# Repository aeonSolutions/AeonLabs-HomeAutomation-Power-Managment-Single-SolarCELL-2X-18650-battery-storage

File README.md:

[PCB-Prototyping-Catalogue](https://github.com/aeonSolutions/PCB-Prototyping-Catalogue)  >>  [Home-Automation](https://github.com/aeonSolutions/PCB-Prototyping-Catalogue/tree/main/Home-Automation)  >>  [Smart Home Solar Power Management](https://github.com/aeonSolutions/PCB-Prototyping-Catalogue/tree/main/Home-Automation/Smart%20Home%20Solar%20Power%20Management)  >>   Single Solar Cell with two 18650 as Battery Storage

<br>

<p align="right">
 <a href="https://github-com.translate.goog/aeonSolutions/PCB-Prototyping-Catalogue/tree/main?_x_tr_sl=en&_x_tr_tl=pt&_x_tr_hl=en&_x_tr_pto=wapp">Change Language</a> <br>
Last update: 01-12-2023
</p>

# Single Solar Cell with two 18650 as Battery Storage
This is a simple PCB for a direct fit on commercially available 4V to 6V [black solar cell tiles](https://s.click.aliexpress.com/e/_DCSwB9L)  with dimensions up to 124mm wide. This PCB features two 18650 Battery management system intended for indoor usage. In particular to be installed on the top or downside of transparent glass windows at a home or office. This PCB, when assembled with a blue solar cell tile, can be used to power a low voltage 4.2V indoor illumination network using ultra-low power micro LED strips.  For instance [this one](https://s.click.aliexpress.com/e/_DCKg9xJ) sold on AliExpress.   

When connected in series and installed on several windows and networked, can power off the grid with a 4.2V LED illumination on all rooms and compartments at a home or office. During evenings and at night until bedtime. If one intends to use it to power indoors LED illumination during the day is required a High Capacity Power Bank connected to all first tiles of all the series. For instance this [power bank](https://s.click.aliexpress.com/e/_Ddl7nsh) here. 

One important takeway about this prototype project is the ability to be installed on any traditional apartment or home in a big city, requiring  124mm of window glass estate, at the top or at the bottom. And it can connect to existing home automation network or systems. If you prefer, can read this project on Autodesk's Instructables.com website [here](https://www.instructables.com/Single-Solar-Cell-With-Two-18650-As-Battery-Storag/).

<p align="center">

</p>

A brief view of specifications:

- 2x 18650 LiPo battery management system
- the PCB can be connected in series to form a length of solar cell tiles packed together (each with its own single BMS.
- Main ON/OFF switch.
- PCB assembly in series made with a 10-pin header/ socket. For "plug and play" type of installations
- Screw terminal to connect main low power 5V DC line at home/office.

<br>

**Status**

This PCB electronics is now fully tested and working when connected to a 5V solar tile and is able to charge a 4.2V LiPo battery. Mind you, this is the simplest electronics, with a restriction, one of being only useful for 24H energy storage (LiPo), meaning this electronics is only capable of managing the solar electricity collected during the day, to run during evenings and also at night until the battery is depleted. Therefore is suited for indoor LED illumination and even suited to power small smart electronics/devices. 

<br>

## PCB

<br>

## Compatibility

<p align="center">

</p>

<br>

## What one additionally needs
-  home tools
-  [transparent double sided tape](https://s.click.aliexpress.com/e/_DDJxMmD)
-  [blue solar cell tiles](https://s.click.aliexpress.com/e/_DCnJW0V)
-  [ultra-low power micro LED strips](https://s.click.aliexpress.com/e/_DCKg9xJ) 
-  [ultra-low power  LED Cob strips](https://s.click.aliexpress.com/e/_DnqkC4N)
-  [Nylon Guide for Electric Cable](https://s.click.aliexpress.com/e/_DBc1oVX)
-  [NCR18650B 3.7V 3400 mah 18650 Lithium](https://s.click.aliexpress.com/e/_DCh1sw1)
-  [Low power electrical wire](https://s.click.aliexpress.com/e/_DB1T3eN)
-  [16A Electrical Plug Wall Socket 110~250V Dual USB 2000mA Port](https://s.click.aliexpress.com/e/_DlVz3sh)
-  [Soldering iron](https://s.click.aliexpress.com/e/_DnDN8x3)
-  [Solder](https://s.click.aliexpress.com/e/_DlXtKMN)
- [power bank](https://s.click.aliexpress.com/e/_Ddl7nsh) 

<br />
<br />

## Author

You can get in touch with me on my LinkedIn Profile:

#### Miguel Tomas

You can also follow my GitHub Profile to stay updated about my latest projects: 

<br>

### Be supportive of my dedication and work towards technology education and buy me a cup of coffee
The PCB Desgin Files i provide here for anyone to use are free. If you like this Smart Device or use it, please consider buying me a cup of coffee, a slice of pizza or a book to help me study, eat and think new PCB design files.

<br />

### Make a donation on Paypal
Make a donation on paypal and get a TAX refund*.

<br>

### Support all these open hardware projects and become a patreon  
Liked any of my PCB KiCad Designs? Help and Support my open work to all by becomming a LDAD Patreon.
In return I will give a free PCB design in KiCad to all patreon supporters. To learn more go to patreon.com. Link below.

<br />
<br />

______________________________________________________________________________________________________________________________
### License
Before proceeding to download any of AeonLabs software solutions for open-source development and/or PCB hardware electronics development make sure you are choosing the right license for your project. See [AeonLabs Solutions for Open Hardware & Source Development](https://github.com/aeonSolutions/PCB-Prototyping-Catalogue/wiki/AeonLabs-Solutions-for-Open-Hardware-&-Source-Development) for more information.

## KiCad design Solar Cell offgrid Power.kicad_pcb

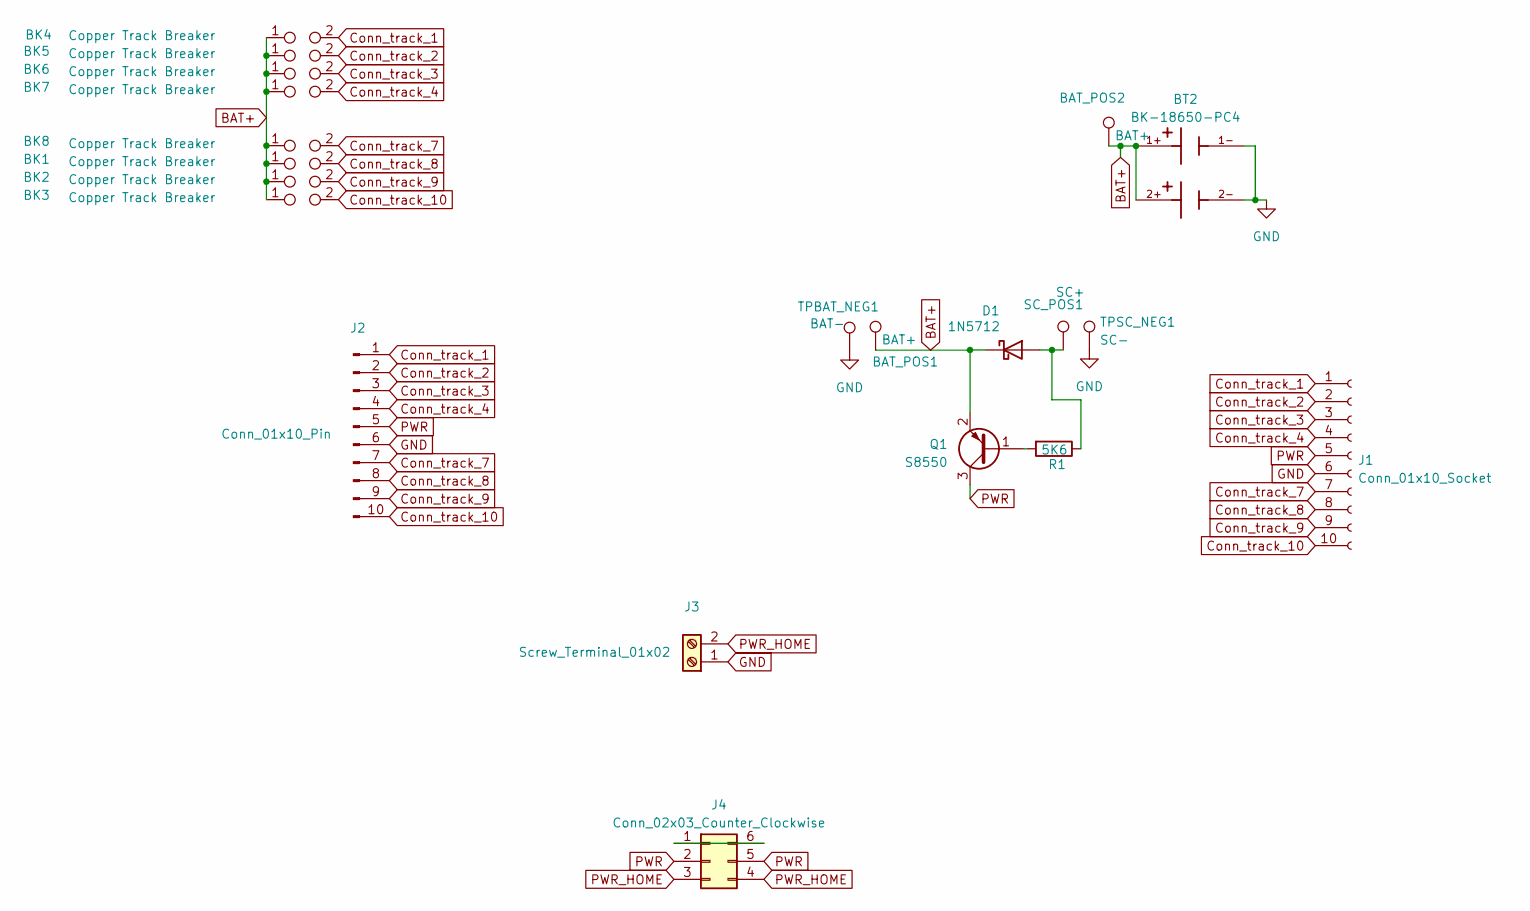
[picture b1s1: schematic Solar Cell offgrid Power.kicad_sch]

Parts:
BAT_POS1, BAT_POS2: BAT+; TestPoint_Pad_3.0x3.0mm
BK1, BK2, BK3, BK4, BK5, BK6, BK7, BK8: Copper Track Breaker; Copper Track Breaker 2 points
BT2: BK-18650-PC4; 2x 18650 Battery holder BAT_BK-18650-PC4; PARTREV K
D1: 1N5712; D_SOD-123
J1: Conn_01x10_Socket; PinSocket_1x10_P2.54mm_Horizontal
J2: Conn_01x10_Pin; PinHeader_1x10_P2.54mm_Horizontal
J3: Screw_Terminal_01x02; TerminalBlock_Phoenix_MPT-0,5-2-2.54_1x02_P2.54mm_Horizontal
J4: Conn_02x03_Counter_Clockwise; Toggle Switch 2 pos PCB MSS-22D18G2 2P2T
Q1: S8550; SOT-23-3
R1: 5K6; R_1210_3225Metric
SC_POS1: SC+; TestPoint_Pad_3.0x3.0mm
TPBAT_NEG1: BAT-; TestPoint_Pad_3.0x3.0mm
TPSC_NEG1: SC-; TestPoint_Pad_3.0x3.0mm

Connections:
BAT+: BAT_POS1.1, BAT_POS2.1, BK1.1, BK2.1, BK3.1, BK4.1, BK5.1, BK6.1, BK7.1, BK8.1, BT2.1+, BT2.2+, D1.1 (K), Q1.2 (E)
Conn_track_1: BK4.2, J1.1, J2.1
Conn_track_2: BK5.2, J1.2, J2.2
Conn_track_3: BK6.2, J1.3, J2.3
Conn_track_4: BK7.2, J1.4, J2.4
Conn_track_7: BK8.2, J1.7, J2.7
Conn_track_8: BK1.2, J1.8, J2.8
Conn_track_9: BK2.2, J1.9, J2.9
Conn_track_10: BK3.2, J1.10, J2.10
GND: BT2.1-, BT2.2-, J1.6, J2.6, J3.1, TPBAT_NEG1.1, TPSC_NEG1.1
unnamed: D1.2 (A), R1.1, SC_POS1.1
unnamed: J4.1, J4.6
unnamed: Q1.1 (B), R1.2
PWR: J1.5, J2.5, J4.2, J4.5, Q1.3 (C)
PWR_HOME: J3.2, J4.3, J4.4

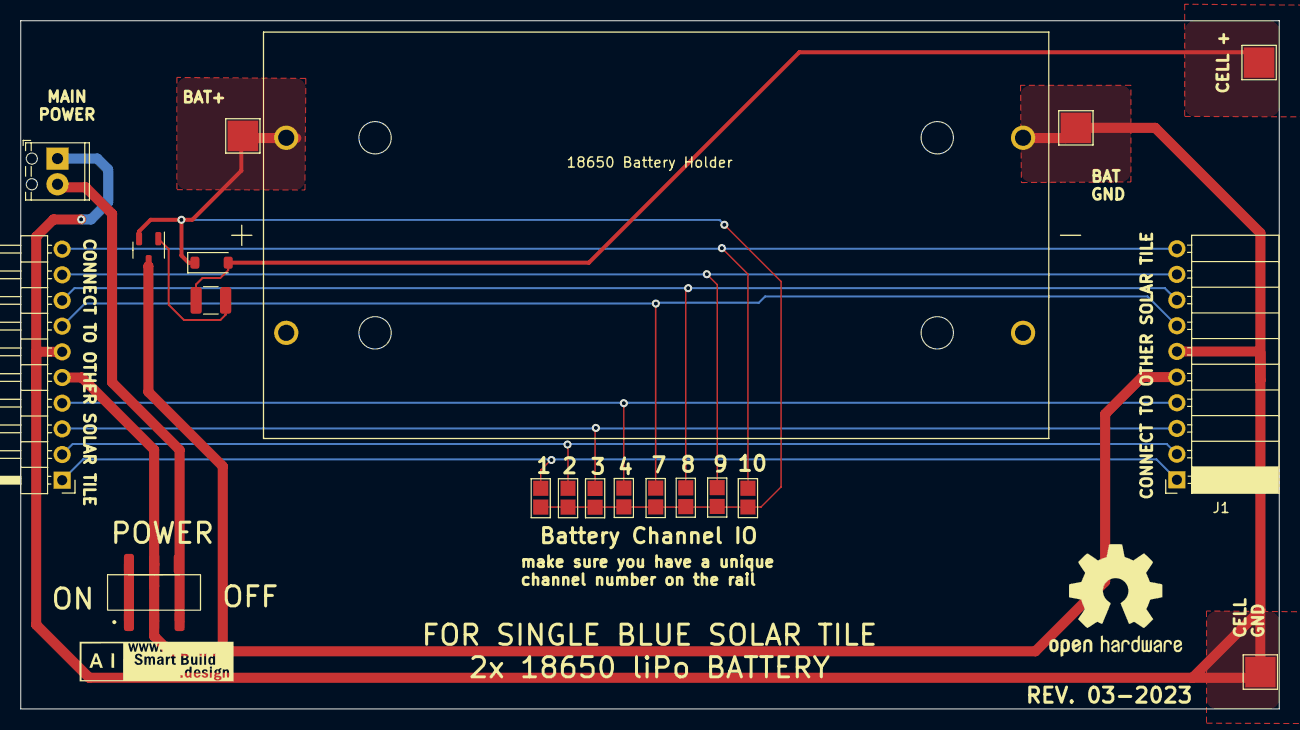
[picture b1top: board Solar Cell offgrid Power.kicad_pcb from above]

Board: 2 copper layers, 124.5 x 68.1 mm, 20 parts (0 on the bottom side), 15 nets.
